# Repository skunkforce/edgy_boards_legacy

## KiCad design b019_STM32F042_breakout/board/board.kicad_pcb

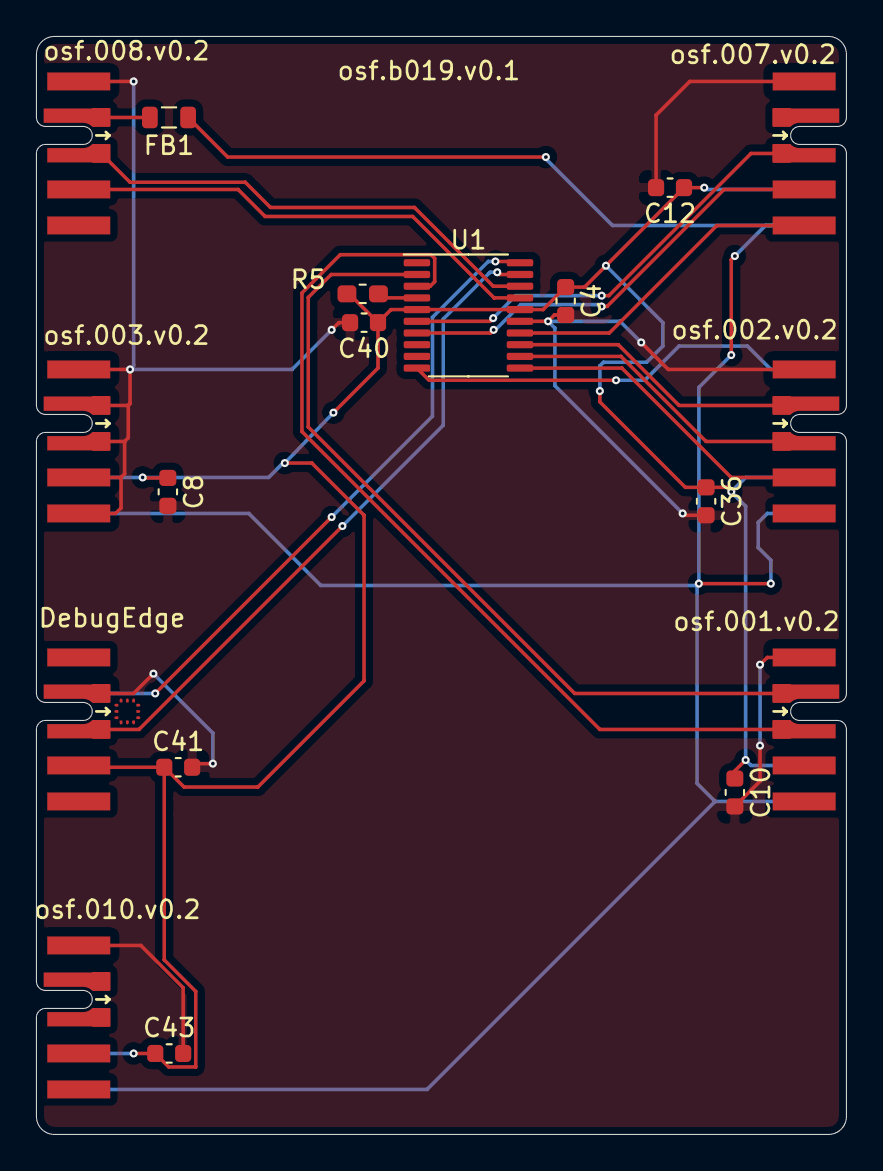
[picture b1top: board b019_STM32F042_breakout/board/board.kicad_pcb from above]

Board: 2 copper layers, 45.0 x 61.0 mm, 18 parts (0 on the bottom side), 18 nets.

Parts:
C4, C10, C12, C36, C40: 100nF; C_0603_1608Metric
C8, C41, C43: 1uF; C_0603_1608Metric
FB1: FCM1608KF-601T03 TypeA; L_0805_2012Metric
J1: 008_USB; on_edge_2x05_device
J2: DebugEdge_02x05; on_edge_2x05_device
J3: 003_power_2x2; on_edge_2x05_device
J6: 010_UART; on_edge_2x05_device
J7: 007_ADC_2x5; on_edge_2x05_host
J8: 001_I2C_2x5; on_edge_2x05_host
J9: 002_SPI_2x5; on_edge_2x05_host
R5: 10k; R_0603_1608Metric_Pad1.05x0.95mm_HandSolder
U1: STM32F042F4Px; TSSOP-20_4.4x6.5mm_P0.65mm

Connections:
+3V3: C4.1, C8.1, C10.1, C12.1, C36.1, C40.1, C41.1, C43.1, J2.5, J3.9, J6.9, J7.9, J8.9, J9.9, R5.2, U1.5, U1.16
+5V: FB1.1, J3.10, J6.10, J7.10, J8.10, J9.10
/uC/AD0: J7.3, U1.6
/uC/AD1: J7.4, U1.7
/uC/AD9: J7.5, U1.14
/uC/D+: J1.3, U1.18
/uC/D-: J1.4, U1.17
/uC/I2C1_SCL: J8.3, U1.3
/uC/I2C1_SDA: J8.2, U1.2
/uC/SPI1_CS: J9.6, U1.10
/uC/SPI1_MISO: J9.3, U1.12
/uC/SPI1_MOSI: J9.2, U1.13
/uC/SPI1_SCK: J9.4, U1.11
/uC/SWCLK: J2.3, U1.20
/uC/SWDIO: J2.2, U1.19
GND: C4.2, C8.2, C10.2, C12.2, C36.2, C40.2, C41.2, C43.2, J1.1, J2.1, J3.1, J3.2, J3.3, J3.4, J3.5, J6.1, J7.1, J8.1, J9.1, U1.15
unnamed: FB1.2, J1.2
unnamed: R5.1, U1.4

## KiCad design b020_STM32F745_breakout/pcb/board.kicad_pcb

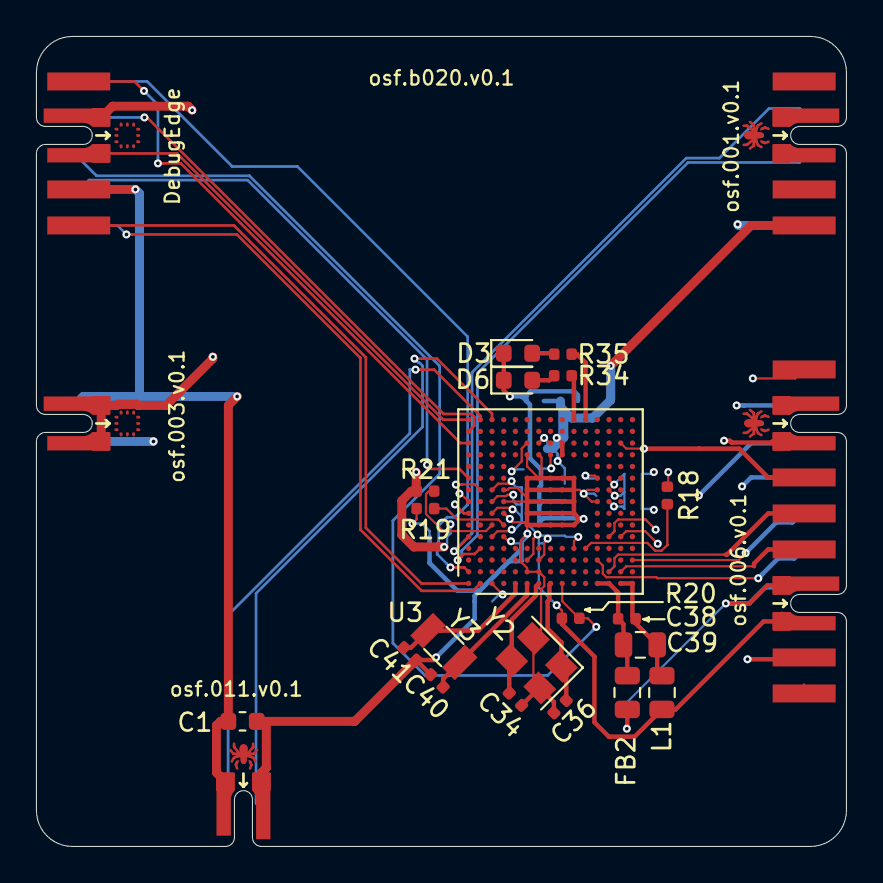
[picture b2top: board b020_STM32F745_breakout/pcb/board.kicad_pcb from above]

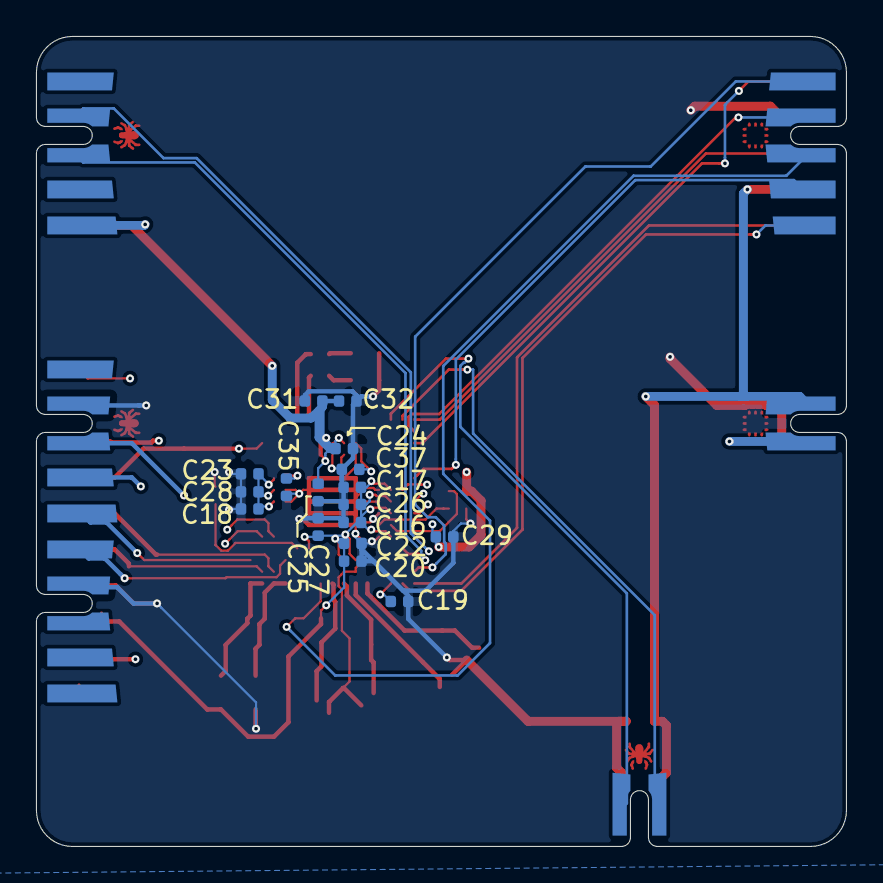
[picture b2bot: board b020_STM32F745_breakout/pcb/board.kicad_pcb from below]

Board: 4 copper layers, 45.0 x 45.0 mm, 42 parts (17 on the bottom side), 39 nets.

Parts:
C1: 10uF; C_0603_1608Metric
C16, C22, C25, C38: 1uF; C_0402_1005Metric
C17, C18, C19, C20, C23, C24, C26, C27, C28, C29, C31, C32: 100nF; C_0402_1005Metric
C34, C36, C40, C41: 22pF; C_0402_1005Metric
C35, C37: 2.2uF; C_0402_1005Metric
C39: 2.2uF; C_0805_2012Metric
D3, D6: LED; LED_0603_1608Metric
FB2: BLM; L_0805_2012Metric
J1: 003_power_2x2; on_edge_2x02_device
J2: I2C_2x2; on_edge_2x05_host
J3: DebugEdge_02x05; on_edge_2x05_device
J4: 006_RMII_2x10; on_edge_2x10_host
J6: 011_GPIO_2x2; on_edge_2x02_host
L1: FCM1608KF-601T03 TypeA; L_0805_2012Metric
R18, R19, R20, R21: 10k; R_0402_1005Metric
R34, R35: 270R; R_0402_1005Metric
U3: STM32F745IEKx; UFBGA-201_10x10mm_Layout15x15_P0.65mm
Y2: Crystal_GND24; Crystal_SMD_Abracon_ABM8G-4Pin_3.2x2.5mm
Y3: Crystal 32kHz; Crystal_SMD_3215-2Pin_3.2x1.5mm

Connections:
+3V3: C1.1, C16.1, C17.1, C18.1, C19.1, C20.1, C22.1, C23.1, C24.1, C25.1, C26.1, C27.1, C28.1, C29.1, C31.1, C32.1, J1.3, J2.9, J3.5, J4.12, J6.2, L1.2, R20.2, R21.2, U3.C1, U3.C5, U3.C7, U3.C8, U3.C9, U3.F3, U3.G3, U3.G13, U3.H13, U3.J12, U3.J13, U3.K4, U3.N8, U3.N9, U3.N10
+5V: J1.4, J2.10
/uC/CRS_DV: J4.10, U3.R3
/uC/GNDA: C38.2, C39.2, FB2.1, U3.M1, U3.N1
/uC/I2C1_SCL: J2.3, U3.A5
/uC/I2C1_SDA: J2.4, U3.B4
/uC/INT_REFCLK: J4.9, U3.N2
/uC/MDC: J4.18, U3.M3
/uC/MDIO: J4.17, U3.P2
/uC/PA11: J6.3, U3.C15
/uC/PA12: J6.4, U3.B15
/uC/RXD0: J4.4, U3.N5
/uC/RXD1: J4.6, U3.P5
/uC/TDI: J3.7, U3.A13
/uC/TRACECLK: J3.8, U3.A2
/uC/TRACED0: J3.9, U3.A1
/uC/TRACED1: J3.10, U3.B1
/uC/TXD0: J4.2, U3.A8
/uC/TXD1: J4.5, U3.A7
/uC/TXEN: J4.7, U3.B9
/uC/nrst: J3.4, J4.15, R20.1, U3.J1
/uC/tck: J3.3, U3.A14
/uC/tdo: J3.6, U3.A10
/uC/tms: J3.2, U3.A15
/uC/vref+: C38.1, C39.1, L1.1, U3.P1, U3.R1
/uC/xtal+: C34.2, U3.G1, Y2.3
/uC/xtal-: C36.1, U3.H1, Y2.1
/uC/xtal_32kHz+: C41.1, U3.E1, Y3.2
/uC/xtal_32kHz-: C40.1, U3.F1, Y3.1
GND: C1.2, C16.2, C17.2, C18.2, C19.2, C20.2, C22.2, C23.2, C24.2, C25.2, C26.2, C27.2, C28.2, C29.2, C31.2, C32.2, C34.1, C35.2, C36.2, C37.2, C40.2, C41.2, D3.1, D6.1, FB2.2, J1.1, J1.2, J3.1, J4.1, J4.3, J4.11, J4.13, J6.1, R18.2, R19.2, U3.D5, U3.D7, U3.D8, U3.D9, U3.F2, U3.F6, U3.F7, U3.F8, U3.F9, U3.F10, U3.F12, U3.G2, U3.G6, U3.G7, U3.G8, U3.G9, U3.G10, U3.G12, U3.H6, U3.H7, U3.H8, U3.H9, U3.H10, U3.H12, U3.J6, U3.J7, U3.J8, U3.J9, U3.J10, U3.K6, U3.K7, U3.K8, U3.K9, U3.K10, U3.M8, U3.M9, Y2.2, Y2.4
unnamed: C35.1, U3.M10
unnamed: C37.1, U3.F13
unnamed: D3.2, R35.1
unnamed: D6.2, R34.1
unnamed: R18.1, U3.L4
unnamed: R19.1, U3.D6
unnamed: R21.1, U3.C6
unnamed: R34.2, U3.K15
unnamed: R35.2, U3.L15

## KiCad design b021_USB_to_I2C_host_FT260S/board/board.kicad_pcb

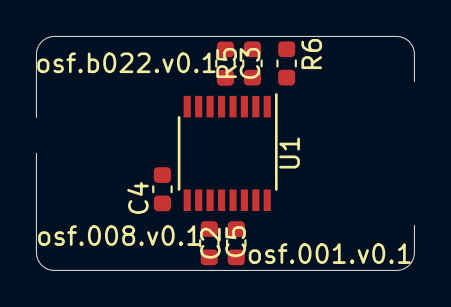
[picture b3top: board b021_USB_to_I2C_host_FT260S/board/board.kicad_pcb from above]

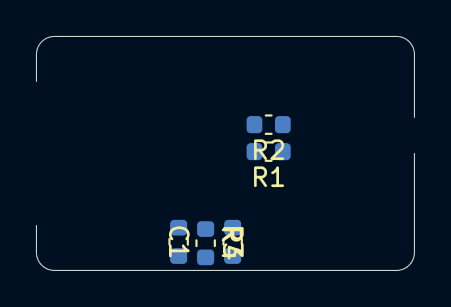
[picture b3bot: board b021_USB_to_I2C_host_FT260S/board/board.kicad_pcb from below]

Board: 4 copper layers, 21.0 x 13.0 mm, 12 parts (5 on the bottom side), 8 nets, no tracks yet.

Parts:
C1: 10nF; C_0603_1608Metric
C2, C3, C5: 100nF; C_0603_1608Metric
C4: 4.7uF; C_0603_1608Metric
R1, R2: 27R; R_0603_1608Metric
R3, R4, R5, R6: 1k; R_0603_1608Metric
U1: FT201XS; SSOP-16_3.9x4.9mm_P0.635mm

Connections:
+3V3: C2.1, C3.1, R5.1, R6.1, U1.3, U1.10
+5V: C4.1, C5.1, R3.1, U1.12
/Sheet603703E3/SCL: R6.2, U1.2
/Sheet603703E3/SDA: R5.2, U1.4
GND: C1.2, C2.2, C3.2, C4.2, C5.2, R4.2, U1.5, U1.13
unnamed: C1.1, R3.2, R4.1, U1.11
unnamed: R1.2, U1.9
unnamed: R2.2, U1.8

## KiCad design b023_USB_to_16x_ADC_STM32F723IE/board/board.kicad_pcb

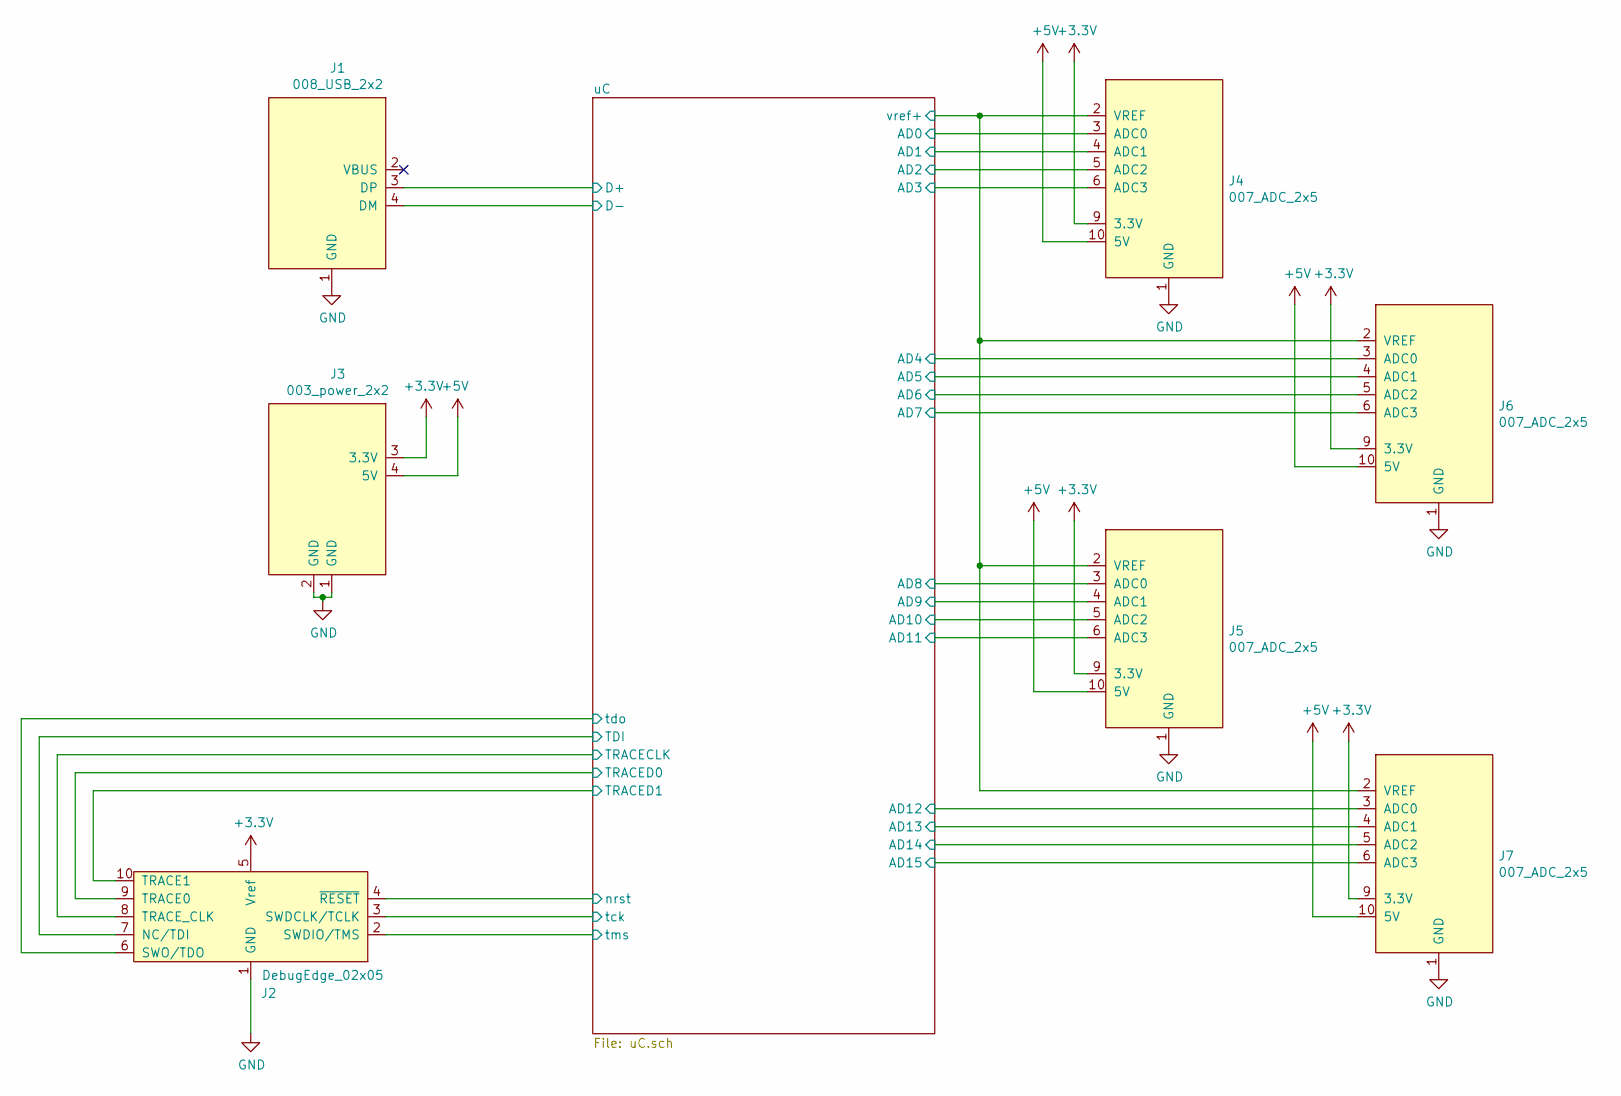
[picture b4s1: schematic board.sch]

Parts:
J1: 008_USB_2x2; on_edge_2x02_device
J2: DebugEdge_02x05; on_edge_2x05_device
J3: 003_power_2x2; on_edge_2x02_device
J4, J5, J6, J7: 007_ADC_2x5; on_edge_2x05_host

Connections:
+5V: J3.4 (5V), J4.10 (5V), J5.10 (5V), J6.10 (5V), J7.10 (5V); also elsewhere on the board
/uC/AD0: J4.3 (ADC0); also elsewhere on the board
/uC/AD1: J4.4 (ADC1); also elsewhere on the board
/uC/AD2: J4.5 (ADC2); also elsewhere on the board
/uC/AD3: J4.6 (ADC3); also elsewhere on the board
/uC/AD4: J6.3 (ADC0); also elsewhere on the board
/uC/AD5: J6.4 (ADC1); also elsewhere on the board
/uC/AD6: J6.5 (ADC2); also elsewhere on the board
/uC/AD7: J6.6 (ADC3); also elsewhere on the board
/uC/AD8: J5.3 (ADC0); also elsewhere on the board
/uC/AD9: J5.4 (ADC1); also elsewhere on the board
/uC/AD10: J5.5 (ADC2); also elsewhere on the board
/uC/AD11: J5.6 (ADC3); also elsewhere on the board
/uC/AD12: J7.3 (ADC0); also elsewhere on the board
/uC/AD13: J7.4 (ADC1); also elsewhere on the board
/uC/AD14: J7.5 (ADC2); also elsewhere on the board
/uC/AD15: J7.6 (ADC3); also elsewhere on the board
/uC/D+: J1.3 (DP); also elsewhere on the board
/uC/D-: J1.4 (DM); also elsewhere on the board
/uC/TDI: J2.7 (NC/TDI); also elsewhere on the board
/uC/TRACECLK: J2.8 (TRACE_CLK); also elsewhere on the board
/uC/TRACED0: J2.9 (TRACE0); also elsewhere on the board
/uC/TRACED1: J2.10 (TRACE1); also elsewhere on the board
/uC/nrst: J2.4 (~RESET~); also elsewhere on the board
/uC/tck: J2.3 (SWDCLK/TCLK); also elsewhere on the board
/uC/tdo: J2.6 (SWO/TDO); also elsewhere on the board
/uC/tms: J2.2 (SWDIO/TMS); also elsewhere on the board
/uC/vref+: J4.2 (VREF), J5.2 (VREF), J6.2 (VREF), J7.2 (VREF); also elsewhere on the board
GND: J1.1 (GND), J2.1 (GND), J3.1 (GND), J3.2 (GND), J4.1 (GND), J5.1 (GND), J6.1 (GND), J7.1 (GND); also elsewhere on the board

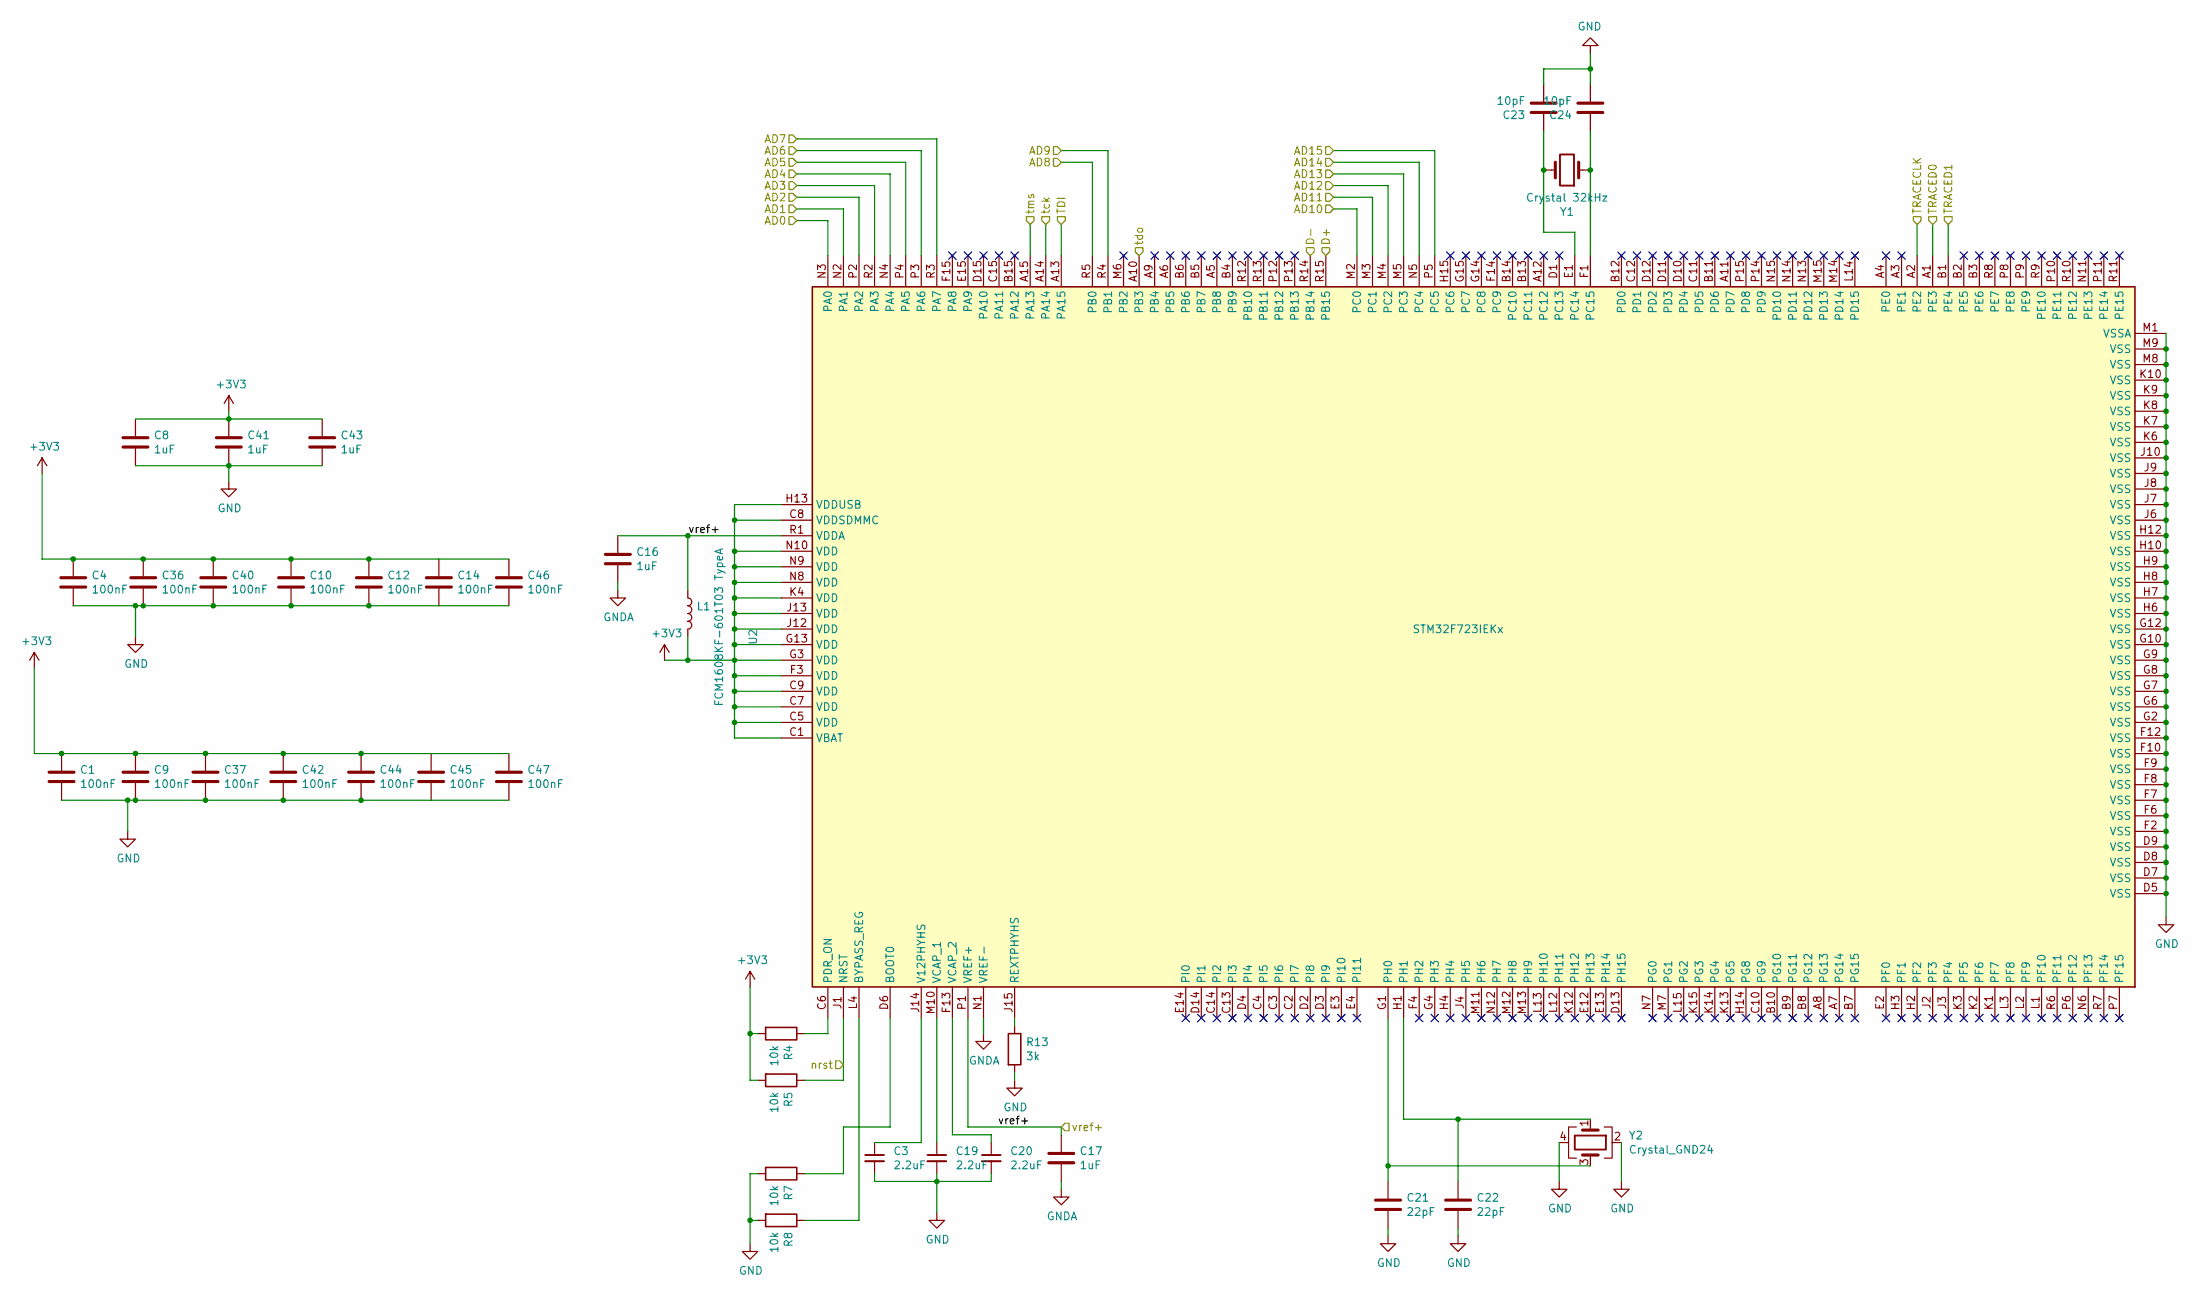
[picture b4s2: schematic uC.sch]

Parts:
C1, C4, C9, C10, C12, C14, C36, C37, C40, C42, C44, C45, C46, C47: 100nF; C_0402_1005Metric
C3, C19, C20: 2.2uF; C_0603_1608Metric_Pad1.05x0.95mm_HandSolder
C8, C16, C17, C41, C43: 1uF; C_0402_1005Metric
C21, C22: 22pF; C_0603_1608Metric_Pad1.05x0.95mm_HandSolder
C23, C24: 10pF; C_0603_1608Metric_Pad1.05x0.95mm_HandSolder
L1: FCM1608KF-601T03 TypeA; L_0805_2012Metric
R4, R5, R7, R8: 10k; R_0603_1608Metric_Pad1.05x0.95mm_HandSolder
R13: 3k; R_0603_1608Metric_Pad1.05x0.95mm_HandSolder
U2: STM32F723IEKx; UFBGA-201_10x10mm_Layout15x15_P0.65mm; MPN STM32F723IEKx; Digi-Key_PN 497-17186-ND
Y1: Crystal 32kHz; Crystal_SMD_3215-2Pin_3.2x1.5mm; Digi-Key_PN 644-1156-1-ND
Y2: Crystal_GND24; Crystal_SMD_Abracon_ABM8G-4Pin_3.2x2.5mm; Digi-Key_PN 535-9140-1-ND

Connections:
/uC/AD0: U2.N3 (PA0); also elsewhere on the board
/uC/AD1: U2.N2 (PA1); also elsewhere on the board
/uC/AD2: U2.P2 (PA2); also elsewhere on the board
/uC/AD3: U2.R2 (PA3); also elsewhere on the board
/uC/AD4: U2.N4 (PA4); also elsewhere on the board
/uC/AD5: U2.P4 (PA5); also elsewhere on the board
/uC/AD6: U2.P3 (PA6); also elsewhere on the board
/uC/AD7: U2.R3 (PA7); also elsewhere on the board
/uC/AD8: U2.R5 (PB0); also elsewhere on the board
/uC/AD9: U2.R4 (PB1); also elsewhere on the board
/uC/AD10: U2.M2 (PC0); also elsewhere on the board
/uC/AD11: U2.M3 (PC1); also elsewhere on the board
/uC/AD12: U2.M4 (PC2); also elsewhere on the board
/uC/AD13: U2.M5 (PC3); also elsewhere on the board
/uC/AD14: U2.N5 (PC4); also elsewhere on the board
/uC/AD15: U2.P5 (PC5); also elsewhere on the board
/uC/D+: U2.R15 (PB15); also elsewhere on the board
/uC/D-: U2.R14 (PB14); also elsewhere on the board
/uC/I2C1_SCL: U2.A5 (PB8); also elsewhere on the board
/uC/I2C1_SDA: U2.B4 (PB9); also elsewhere on the board
/uC/I2C3_SCL: U2.F15 (PA8); also elsewhere on the board
/uC/I2C3_SDA: U2.F14 (PC9); also elsewhere on the board
/uC/SPI2_MISO: U2.C14 (PI2); also elsewhere on the board
/uC/SPI2_MOSI: U2.C13 (PI3); also elsewhere on the board
/uC/SPI2_SCK: U2.D11 (PD3); also elsewhere on the board
/uC/SPI5_MISO: U2.L3 (PF8); also elsewhere on the board
/uC/SPI5_MOSI: U2.L2 (PF9); also elsewhere on the board
/uC/SPI5_SCK: U2.K1 (PF7); also elsewhere on the board
/uC/TDI: U2.A13 (PA15); also elsewhere on the board
/uC/TRACECLK: U2.A2 (PE2); also elsewhere on the board
/uC/TRACED0: U2.A1 (PE3); also elsewhere on the board
/uC/TRACED1: U2.B1 (PE4); also elsewhere on the board
/uC/nrst: R5.1, U2.J1 (NRST); also elsewhere on the board
/uC/tck: U2.A14; also elsewhere on the board
/uC/tdo: U2.A10 (PB3); also elsewhere on the board
/uC/tms: U2.A15 (PA13); also elsewhere on the board
/uC/vref+: C16.1, C17.1, L1.1, U2.P1 (VREF+), U2.R1 (VDDA); also elsewhere on the board
GND: C1.2, C3.2, C4.2, C8.2, C9.2, C10.2, C12.2, C14.2, C19.2, C20.2, C21.2, C22.2, C23.2, C24.2, C36.2, C37.2, C40.2, C41.2, C42.2, C43.2, C44.2, C45.2, C46.2, C47.2, R7.2, R8.2, R13.2, U2.D5 (VSS), U2.D7 (VSS), U2.D8 (VSS), U2.D9 (VSS), U2.F2 (VSS), U2.F6 (VSS), U2.F7 (VSS), U2.F8 (VSS), U2.F9 (VSS), U2.F10 (VSS), U2.F12 (VSS), U2.G2 (VSS), U2.G6 (VSS), U2.G7 (VSS), U2.G8 (VSS), U2.G9 (VSS), U2.G10 (VSS), U2.G12 (VSS), U2.H6 (VSS), U2.H7 (VSS), U2.H8 (VSS), U2.H9 (VSS), U2.H10 (VSS), U2.H12 (VSS), U2.J6 (VSS), U2.J7 (VSS), U2.J8 (VSS), U2.J9 (VSS), U2.J10 (VSS), U2.K6 (VSS), U2.K7 (VSS), U2.K8 (VSS), U2.K9 (VSS), U2.K10 (VSS), U2.M1 (VSSA), U2.M8 (VSS), U2.M9 (VSS), Y2.2, Y2.4; also elsewhere on the board
GNDA: C16.2, C17.2, U2.N1 (VREF-)
unnamed: C3.1, U2.J14 (V12PHYHS)
unnamed: C19.1, U2.M10 (VCAP_1)
unnamed: C20.1, U2.F13 (VCAP_2)
unnamed: C21.1, U2.G1 (PH0), Y2.3
unnamed: C22.1, U2.H1, Y2.1
unnamed: C23.1, U2.E1 (PC14), Y1.2
unnamed: C24.1, U2.F1 (PC15), Y1.1
unnamed: R4.1, U2.C6 (PDR_ON)
unnamed: R7.1, U2.D6 (BOOT0)
unnamed: R8.1, U2.L4 (BYPASS_REG)
unnamed: R13.1, U2.J15 (REXTPHYHS)

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
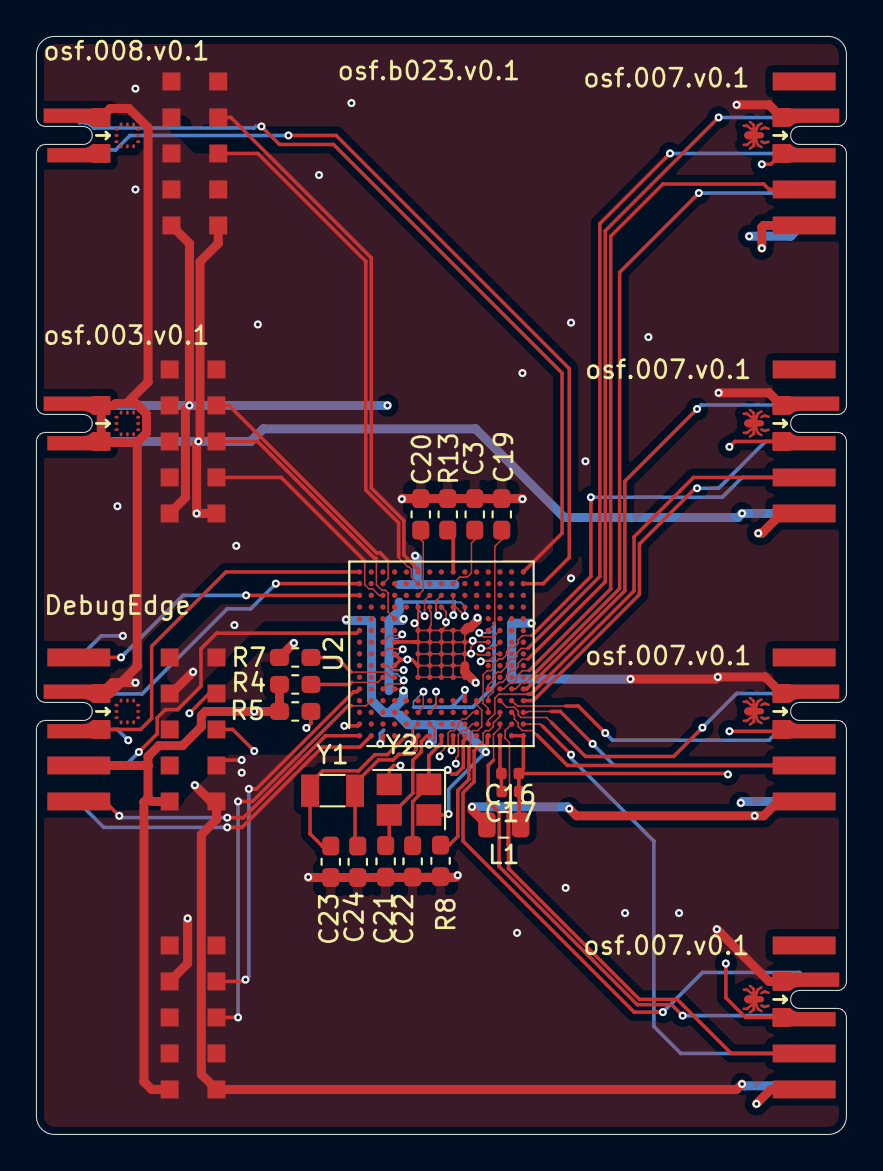
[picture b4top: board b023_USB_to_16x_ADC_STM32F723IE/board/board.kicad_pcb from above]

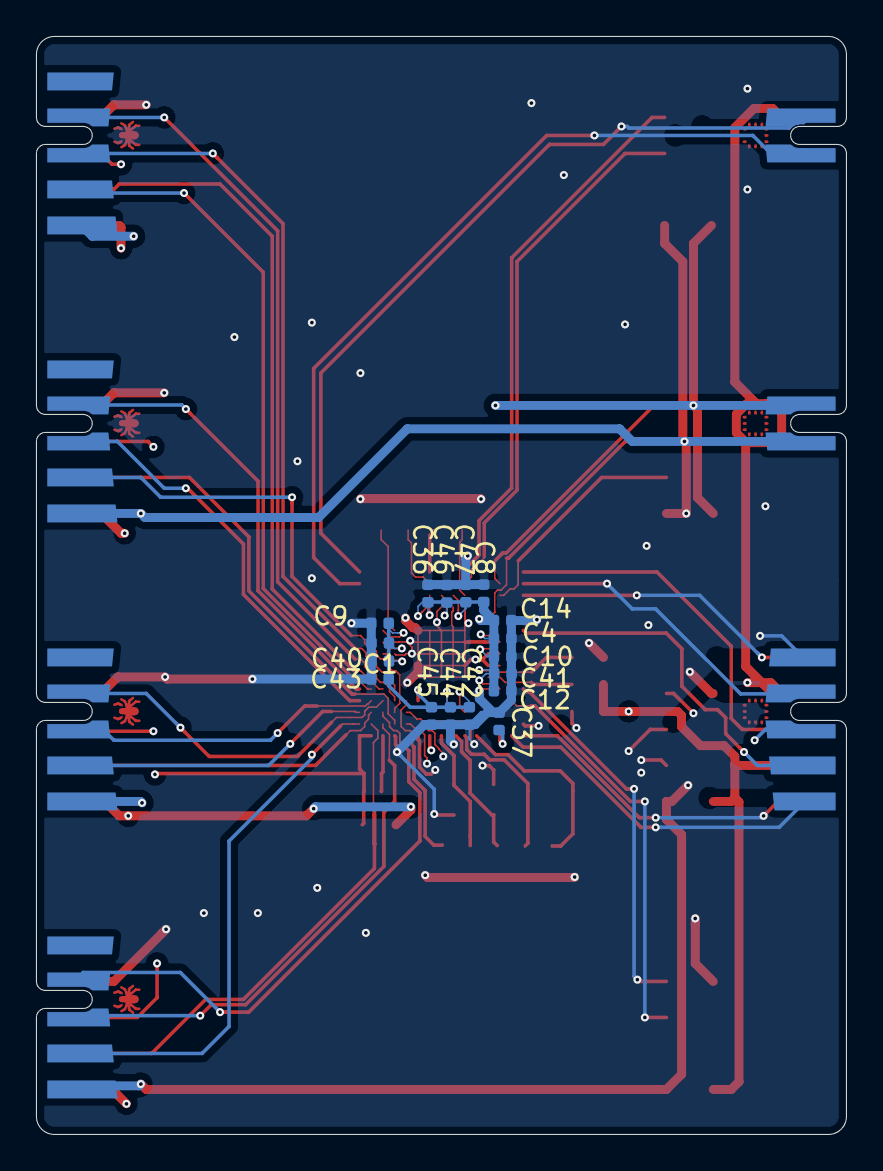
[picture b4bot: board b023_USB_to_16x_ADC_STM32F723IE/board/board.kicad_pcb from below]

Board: 4 copper layers, 45.0 x 61.0 mm, 46 parts (17 on the bottom side), 52 nets.

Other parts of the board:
J8, J10: 001_I2C_2x5; on_edge_2x05_up_host
J9, J11: 002_SPI_2x5; on_edge_2x05_up_host

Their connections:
+5V: J8.10, J9.10, J10.10, J11.10; also elsewhere on the board
/uC/I2C1_SCL: J8.3; also elsewhere on the board
/uC/I2C1_SDA: J8.4; also elsewhere on the board
/uC/I2C3_SCL: J10.3; also elsewhere on the board
/uC/I2C3_SDA: J10.4; also elsewhere on the board
/uC/SPI2_MISO: J9.3; also elsewhere on the board
/uC/SPI2_MOSI: J9.6; also elsewhere on the board
/uC/SPI2_SCK: J9.4; also elsewhere on the board
/uC/SPI5_MISO: J11.3; also elsewhere on the board
/uC/SPI5_MOSI: J11.6; also elsewhere on the board
/uC/SPI5_SCK: J11.4; also elsewhere on the board
GND: J8.1, J9.1, J10.1, J11.1; also elsewhere on the board

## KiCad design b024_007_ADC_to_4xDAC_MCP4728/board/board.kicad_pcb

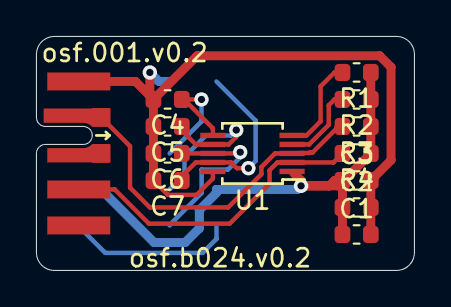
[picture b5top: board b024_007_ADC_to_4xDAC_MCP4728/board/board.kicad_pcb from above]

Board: 2 copper layers, 21.0 x 13.0 mm, 14 parts (0 on the bottom side), 11 nets.

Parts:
C1: 100nF; C_0603_1608Metric
C2: 10nF; C_0603_1608Metric
C3, C4, C5, C6, C7: 1nF; C_0603_1608Metric
J1: 007_ADC_2x5; on_edge_2x05_down_device
J2: 001_I2C_2x5; on_edge_2x05_device
R1, R2, R3, R4: 5k; R_0603_1608Metric
U1: MCP4728; MSOP-10_3x3mm_P0.5mm

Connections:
GND: C1.2, C2.2, C3.2, C4.2, C5.2, C6.2, C7.2, J1.1, J2.1, U1.10
unnamed: C4.1, J1.3, U1.6
unnamed: C5.1, J1.4, U1.7
unnamed: C6.1, J1.5, U1.8
unnamed: C7.1, J1.6, U1.9
unnamed: J1.10, J2.10
unnamed: J2.2, R3.2, U1.3
unnamed: J2.4, R4.2, U1.2
unnamed: R1.2, U1.5
unnamed: R2.2, U1.4
VCC: C1.1, C2.1, C3.1, J1.9, J2.9, R1.1, R2.1, R3.1, R4.1, U1.1

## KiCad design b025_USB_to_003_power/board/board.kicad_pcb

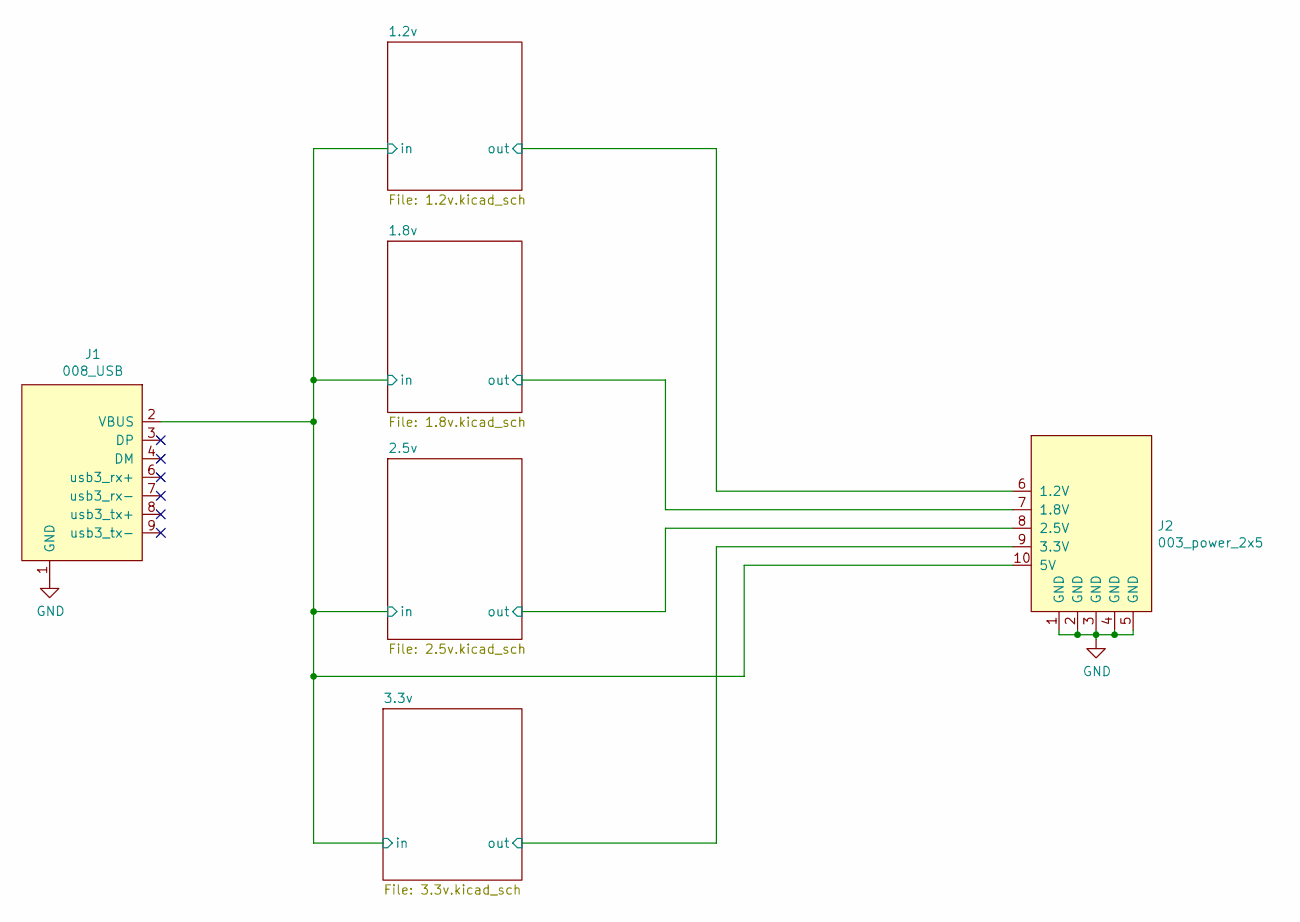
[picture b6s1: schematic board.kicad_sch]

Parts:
J1: 008_USB; on_edge_2x05_device
J2: 003_power_2x5; on_edge_2x05_host

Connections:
/1.2v/in: J1.2 (VBUS), J2.10 (5V); also elsewhere on the board
/1.2v/out: J2.6 (1.2V); also elsewhere on the board
/1.8v/out: J2.7 (1.8V); also elsewhere on the board
/2.5v/out: J2.8 (2.5V); also elsewhere on the board
/3.3v/out: J2.9 (3.3V); also elsewhere on the board
GND: J1.1 (GND), J2.1 (GND), J2.2 (GND), J2.3 (GND), J2.4 (GND), J2.5 (GND); also elsewhere on the board

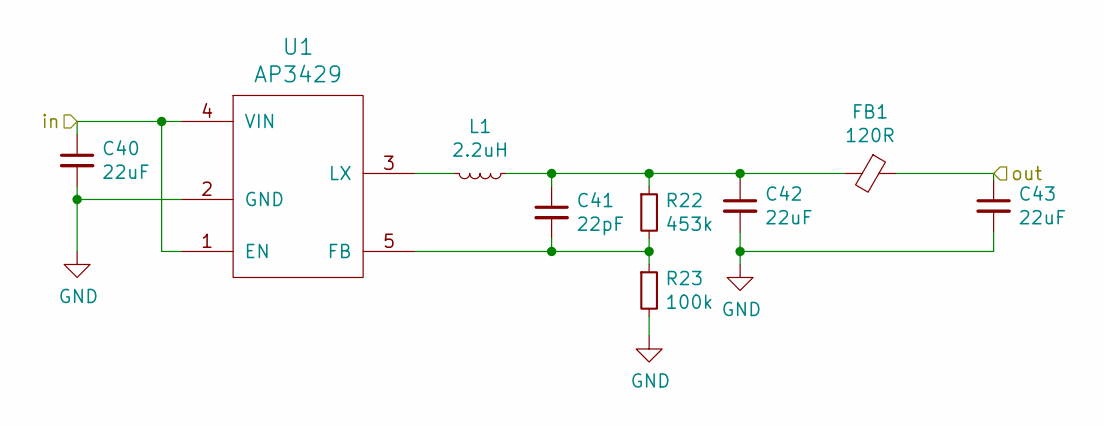
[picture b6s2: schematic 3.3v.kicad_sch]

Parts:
C40, C42, C43: 22uF; C_0603_1608Metric
C41: 22pF; C_0402_1005Metric
FB1: 120R; R_0603_1608Metric
L1: 2.2uH; L_Taiyo-Yuden_NR-50xx; MPN NRS5030T2R2NMGJ
R22: 453k; C_0402_1005Metric
R23: 100k; C_0402_1005Metric
U1: AP3429; TSOT-23-5; MPN AP3429AKTTR-G1

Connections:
/1.2v/in: C40.1, U1.1 (EN), U1.4 (VIN); also elsewhere on the board
/3.3v/out: C43.1, FB1.1; also elsewhere on the board
GND: C40.2, C42.2, C43.2, R23.2, U1.2 (GND); also elsewhere on the board
unnamed: C41.1, C42.1, FB1.2, L1.1, R22.1
unnamed: C41.2, R22.2, R23.1, U1.5 (FB)
unnamed: L1.2, U1.3 (LX)

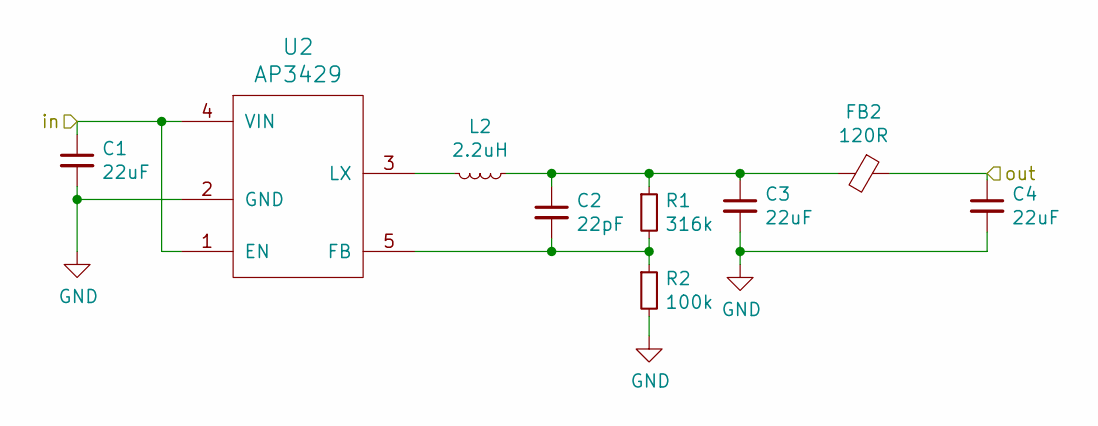
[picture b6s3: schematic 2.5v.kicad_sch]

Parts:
C1, C3, C4: 22uF; C_0603_1608Metric
C2: 22pF; C_0402_1005Metric
FB2: 120R; R_0603_1608Metric
L2: 2.2uH; L_Taiyo-Yuden_NR-50xx; MPN NRS5030T2R2NMGJ
R1: 316k; C_0402_1005Metric
R2: 100k; C_0402_1005Metric
U2: AP3429; TSOT-23-5; MPN AP3429AKTTR-G1

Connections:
/1.2v/in: C1.1, U2.1 (EN), U2.4 (VIN); also elsewhere on the board
/2.5v/out: C4.1, FB2.1; also elsewhere on the board
GND: C1.2, C3.2, C4.2, R2.2, U2.2 (GND); also elsewhere on the board
unnamed: C2.1, C3.1, FB2.2, L2.1, R1.1
unnamed: C2.2, R1.2, R2.1, U2.5 (FB)
unnamed: L2.2, U2.3 (LX)

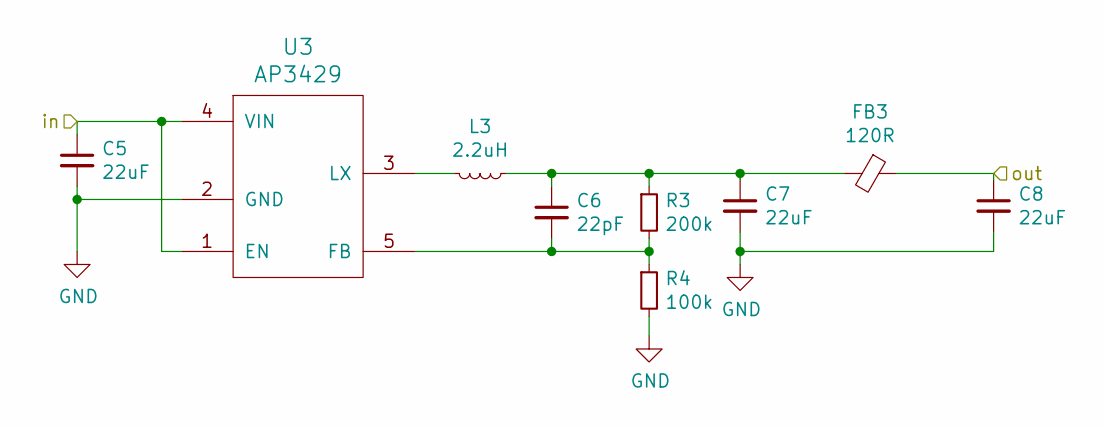
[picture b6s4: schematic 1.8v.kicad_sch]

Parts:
C5, C7, C8: 22uF; C_0603_1608Metric
C6: 22pF; C_0402_1005Metric
FB3: 120R; R_0603_1608Metric
L3: 2.2uH; L_Taiyo-Yuden_NR-50xx; MPN NRS5030T2R2NMGJ
R3: 200k; C_0402_1005Metric
R4: 100k; C_0402_1005Metric
U3: AP3429; TSOT-23-5; MPN AP3429AKTTR-G1

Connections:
/1.2v/in: C5.1, U3.1 (EN), U3.4 (VIN); also elsewhere on the board
/1.8v/out: C8.1, FB3.1; also elsewhere on the board
GND: C5.2, C7.2, C8.2, R4.2, U3.2 (GND); also elsewhere on the board
unnamed: C6.1, C7.1, FB3.2, L3.1, R3.1
unnamed: C6.2, R3.2, R4.1, U3.5 (FB)
unnamed: L3.2, U3.3 (LX)

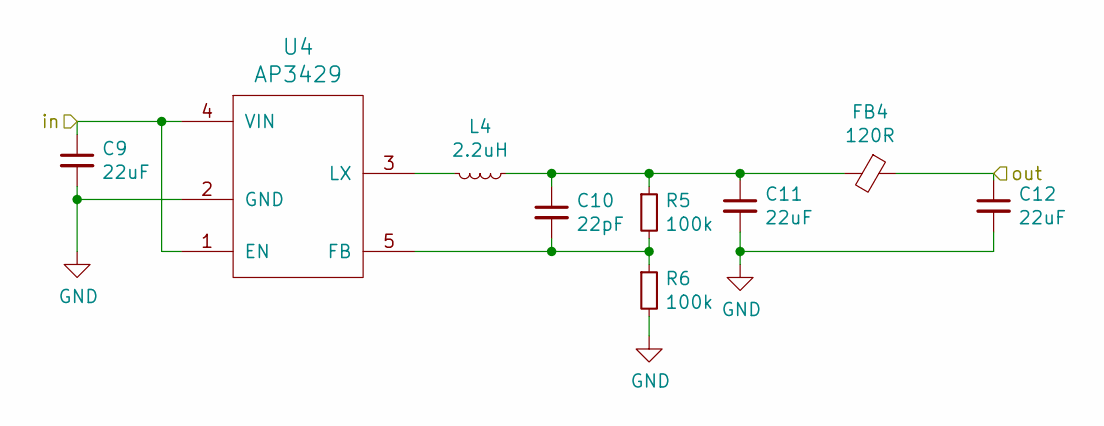
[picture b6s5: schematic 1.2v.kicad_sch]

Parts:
C9, C11, C12: 22uF; C_0603_1608Metric
C10: 22pF; C_0402_1005Metric
FB4: 120R; R_0603_1608Metric
L4: 2.2uH; L_Taiyo-Yuden_NR-50xx; MPN NRS5030T2R2NMGJ
R5, R6: 100k; C_0402_1005Metric
U4: AP3429; TSOT-23-5; MPN AP3429AKTTR-G1

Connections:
/1.2v/in: C9.1, U4.1 (EN), U4.4 (VIN); also elsewhere on the board
/1.2v/out: C12.1, FB4.1; also elsewhere on the board
GND: C9.2, C11.2, C12.2, R6.2, U4.2 (GND); also elsewhere on the board
unnamed: C10.2, R5.2, R6.1, U4.5 (FB)
unnamed: C10.1, C11.1, FB4.2, L4.1, R5.1
unnamed: L4.2, U4.3 (LX)

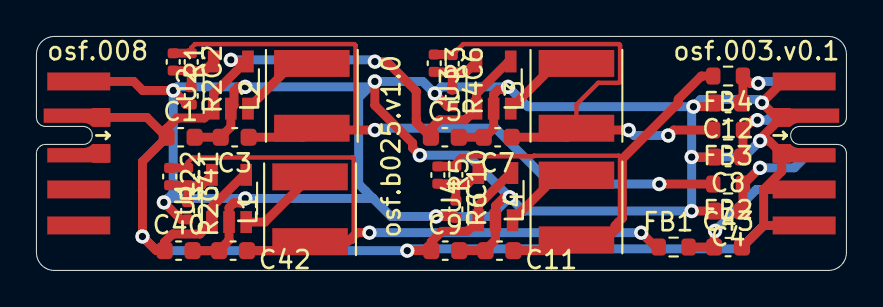
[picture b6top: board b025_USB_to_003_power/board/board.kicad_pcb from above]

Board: 2 copper layers, 45.0 x 13.0 mm, 38 parts (0 on the bottom side), 18 nets.
